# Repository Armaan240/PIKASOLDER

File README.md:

# PIKASOLDER
⚡ Pikachu PCB: Auto LED &amp; Motor Circuit A Pikachu-shaped PCB that lights up LEDs in the dark using an LDR and turns on both LEDs and a vibration motor when a button is pressed in daylight. Powered by a CR2032 coin cell and controlled via a BC547 transistor.

---
### **SLACK ID U091M21518T**
### **SLACK USERNAME @Amu**

### **What This Circuit Does**  
1. **Single-Button Control** (Keychain Switch):  
   - Press the button to **turn on 2 LEDs and the vibrating motor simultaneously**.  
   - Release to turn everything off.  

2. **Automatic Light Sensor (Optional LDR Mode)**:  
   - If you included an LDR, the LEDs can also turn on **automatically in darkness**.  

3. **Compact Design**:  
   - Powered by a **small battery (e.g., coin cell or 3V CR2032)** for portability.
  
   - **Images of The Project**
.png)
.png)
.png)
.png)
.png)

---

## 📦 **Bill of Materials (BoM) – Pikachu PCB Project**

| **#** | **Part Name**               | **Label** | **Value/Type**     | **Package / Footprint**                             | **Qty** |
| ----- | --------------------------- | --------- | ------------------ | --------------------------------------------------- | ------- |
| 1     | NPN Transistor              | Q1 ,Q2    | BC547              | TO-92 (TO-92\_Inline)                               | 2       |
| 2     | Light Dependent Resistor    | LDR       |GL5528 (typical)    | Resistor\_THT\:R-2.5 (or similar photoresistor pad) | 1       |
| 3     | Resistor                    | R1        | 10kΩ               | R\_Axial\_DIN0207\_L6.3mm\_P7.62mm\_Horizontal      | 2       |
| 4     | Resistor                    | R2        | 100Ω – 470Ω        | Same as above                                       | 1       |
| 5     | Red LED                     | L1        | 5mm LED            | LED\_THT\:LED\_D5.0mm                               | 1       |
| 6     | Red LED                     | L2        | 5mm LED            | LED\_THT\:LED\_D5.0mm                               | 1       |
| 7     | Tactile Push Button         | SW1       | 6x6 mm Push Button | Button\_Switch\_THT\:SW\_PUSH\_6mm\_H5mm            | 1       |
| 8     | Coin Vibration Motor        | M1        | 3V Vibration Motor | Connected via header (Conn\_01x02\_Male)            | 1       |
| 9     | Coin Cell Battery Holder    | BT1       | CR2032 Holder      | Battery\_Holder\_Keystone\_3002\_1x20mm             | 1       |
| 10    | Generic Header (Motor Pads) | J1        | 2-pin male header  | Conn\_01x02\_Male or TestPoints                     | 1       |

---

Would you like me to export this BoM in `.csv` or `.xlsx` format ready for JLCPCB/assembly quoting?

### **Design Choices & Challenges**  
#### **Why This Design?**  
- **Keychain Use Case**: You wanted a simple, one-handed operation (no need for two-button safety).  
- **Minimalist Parts**: Reduced components to fit a small enclosure (e.g., keychain or pocket-sized).  

#### **Challenges Faced**  
- **Power Management**: Ensuring the battery can drive both LEDs and motor without draining too fast.  
   - *Fix*: Use low-current LEDs (e.g., 2mA) and a efficient motor (3V pager motor).  
- **Space Constraints**: Fitting everything into a tiny keychain form.  
   - *Fix*: SMD components or tightly arranged through-hole parts.  

#### **What I Learned**  
- **KiCad Tips**:  
  - Use **global labels** (e.g., `+VCC`, `GND`) to avoid messy wires.  
  - **ERC Checks** catch missing power connections early.  
- **Circuit Simplification**: Fewer parts = fewer points of failure.  

---

### **Advice for Beginners**  
1. **Start Simple**:  
   - If this is your **first PCB**, try a **single-LED + button circuit** before adding motors/sensors.  
2. **KiCad Learning Curve**:  
   - Watch tutorials on **schematic symbols** vs. **footprints** (common confusion).  
3. **Test on Breadboard First**:  
   - Verify the circuit works before designing the PCB.  

---

### **Optional Upgrades**  
1. **Add a Timer (555 IC)**:  
   - Make the motor vibrate for **10 seconds after button press**.  
2. **Low-Power Mode**:  
   - Use a **toggle switch** to disable the motor but keep LEDs.  

---

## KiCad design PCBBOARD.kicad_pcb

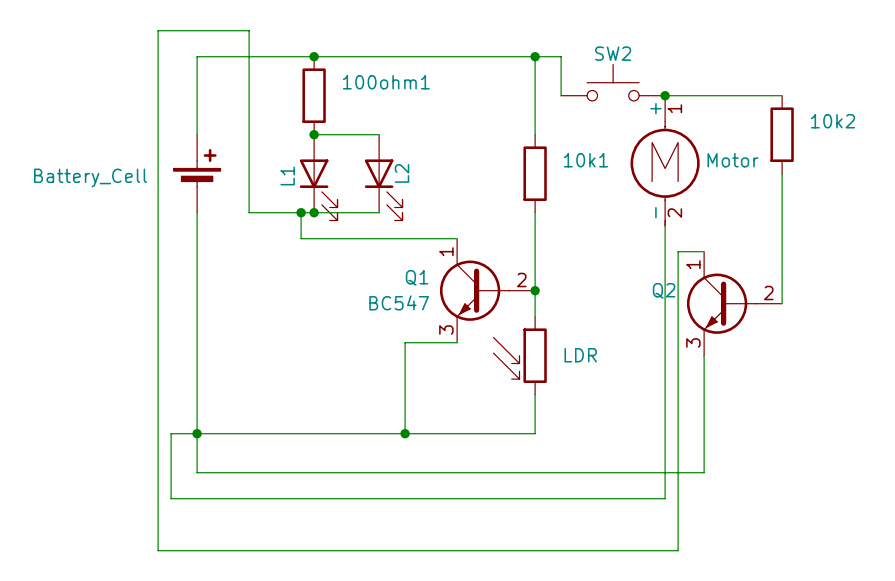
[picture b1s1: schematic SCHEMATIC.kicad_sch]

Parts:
10k1, 10k2, 100ohm1: R1; R_Axial_DIN0207_L6.3mm_D2.5mm_P7.62mm_Horizontal
BT1: Battery_Cell; BatteryHolder_Keystone_3002_1x2032
D2: L2; LED_D5.0mm
L1: LED; LED_D5.0mm
M2: Motor; PinHeader_1x02_P2.54mm_Vertical
Q1, Q2: BC547; TO-92_Inline
R1: LDR; R_LDR_5.0x4.1mm_P3mm_Vertical
SW2: SW_Push; SW_PUSH_6mm_H5mm

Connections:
unnamed: 10k1.1, 100ohm1.1, BT1.1 (+), SW2.1
unnamed: BT1.2 (-), M2.2 (-), Q1.3 (E), Q2.3 (E), R1.2
unnamed: 100ohm1.2, D2.2 (A), L1.2 (A)
unnamed: D2.1 (K), L1.1 (K), Q1.1 (C), Q2.1 (C)
unnamed: 10k2.1, M2.1 (+), SW2.2
unnamed: 10k1.2, Q1.2 (B), R1.1
unnamed: 10k2.2, Q2.2 (B)

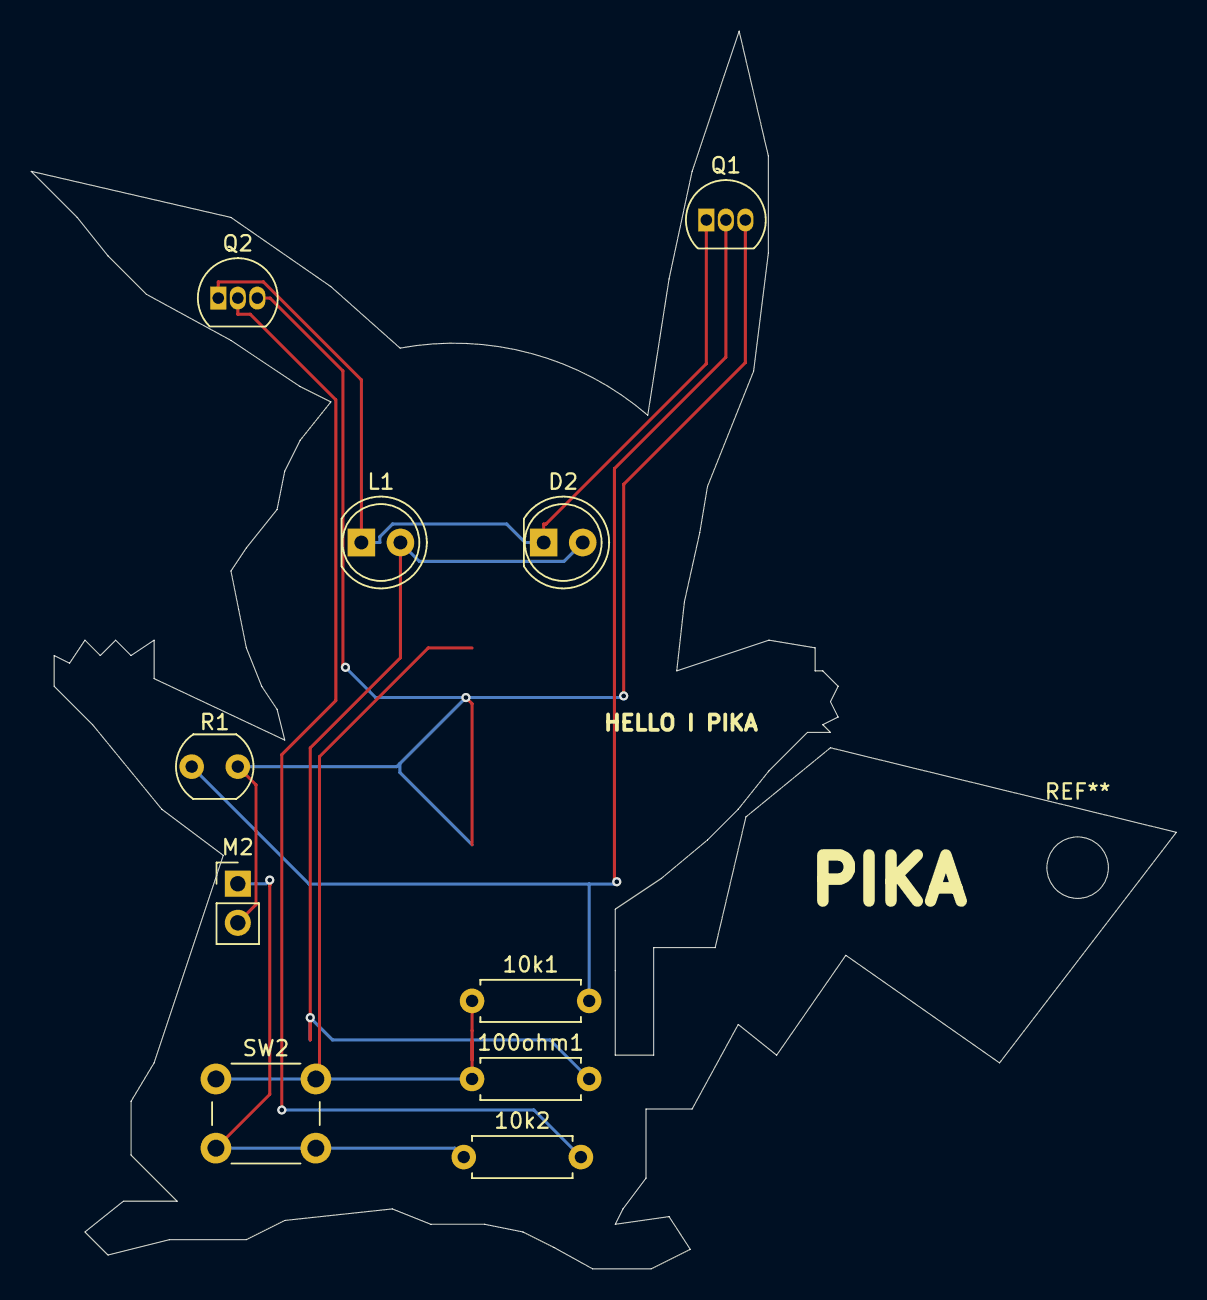
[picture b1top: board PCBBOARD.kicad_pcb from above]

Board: 2 copper layers, 74.5 x 80.5 mm, 11 parts (1 on the bottom side), 7 nets.
